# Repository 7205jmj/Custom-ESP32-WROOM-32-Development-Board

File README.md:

# Custom-ESP32-WROOM-32-Development-Board
A professionally designed ESP32-WROOM-32 Development Board created in KiCad for IoT, Embedded Systems, and Rapid Prototyping applications. This project aims to provide a compact, reliable, and cost-effective alternative to commercial ESP32 development boards while exposing essential GPIOs and integrating the required support circuitry for seamless programming and deployment.

Overview

Most ESP32 development boards available in the market include additional features that may not be required for every project. This custom board was designed to provide a clean and optimized ESP32 platform suitable for learning, prototyping, and product development.

The board integrates:

1.ESP32-WROOM-32 module
2.USB-powered operation
3.On-board 3.3V regulation
4.Auto-programming circuit
5.Reset and Boot buttons
6.Status indication LEDs
7.GPIO breakout headers
8.Compact 2-layer PCB layout

Hardware Specifications
Parameter	Specification
Module--->	ESP32-WROOM-32
CPU	---->Dual-Core Xtensa LX6
Clock Frequency------->	Up to 240 MHz
Flash Memory--------->	As per module variant
Operating Voltage	--->3.3V
Input Voltage---->	5V USB
Wireless-------->	Wi-Fi + Bluetooth
PCB Layers---------->	2
Design Software	--------->KiCad

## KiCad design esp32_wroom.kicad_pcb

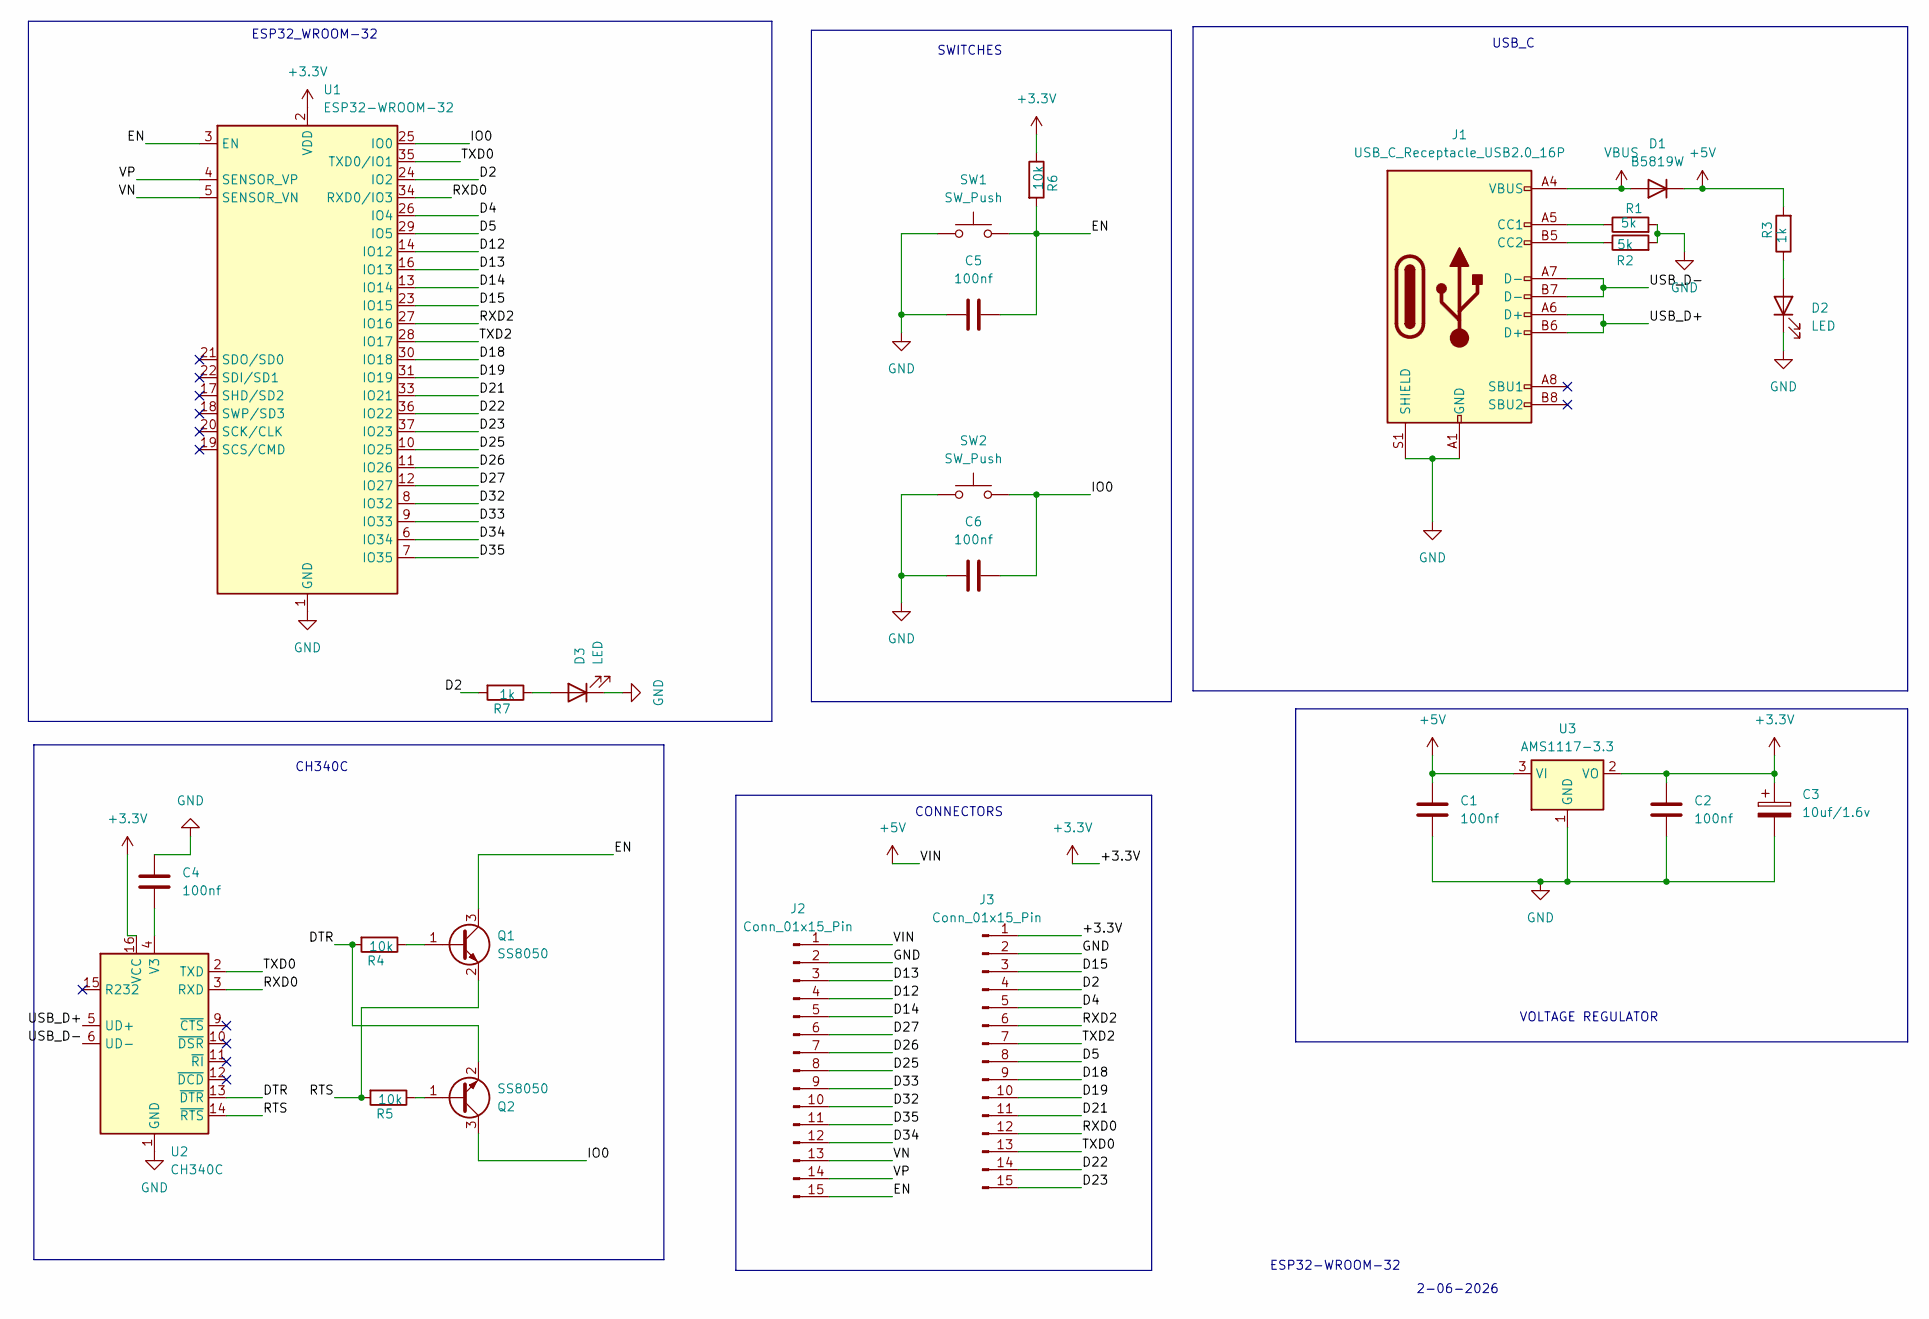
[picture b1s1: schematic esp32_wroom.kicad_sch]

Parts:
C1, C2, C4, C5, C6: 100nf; C_0603_1608Metric
C3: 10uf/1.6v; CP_EIA-3216-10_Kemet-I
D1: B5819W; D_SOD-123
D2, D3: LED; LED_0603_1608Metric
J1: USB_C_Receptacle_USB2.0_16P; USB_C_Receptacle_HRO_TYPE-C-31-M-12
J2, J3: Conn_01x15_Pin; PinHeader_1x15_P2.54mm_Vertical
Q1, Q2: SS8050; SOT-23
R1, R2: 5k; R_0603_1608Metric
R3, R7: 1k; R_0603_1608Metric
R4, R5, R6: 10k; R_0603_1608Metric
SW1, SW2: SW_Push; SW_Push_SPST_NO_Alps_SKRK
U1: ESP32-WROOM-32
U2: CH340C; SOIC-16_3.9x9.9mm_P1.27mm
U3: AMS1117-3.3; SOT-223-3_TabPin2

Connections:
+3.3V: C2.1, C3.1, J3.1, R6.1, U1.2 (VDD), U2.16 (VCC), U3.2 (VO)
+5V: C1.1, D1.1 (K), J2.1, R3.2, U3.3 (VI)
/D2: J3.4, R7.2, U1.24 (IO2)
/D4: J3.5, U1.26 (IO4)
/D5: J3.8, U1.29 (IO5)
/D12: J2.4, U1.14 (IO12)
/D13: J2.3, U1.16 (IO13)
/D14: J2.5, U1.13 (IO14)
/D15: J3.3, U1.23 (IO15)
/D18: J3.9, U1.30 (IO18)
/D19: J3.10, U1.31 (IO19)
/D21: J3.11, U1.33 (IO21)
/D22: J3.14, U1.36 (IO22)
/D23: J3.15, U1.37 (IO23)
/D25: J2.8, U1.10 (IO25)
/D26: J2.7, U1.11 (IO26)
/D27: J2.6, U1.12 (IO27)
/D32: J2.10, U1.8 (IO32)
/D33: J2.9, U1.9 (IO33)
/D34: J2.12, U1.6 (IO34)
/D35: J2.11, U1.7 (IO35)
/DTR: Q2.2 (E), R4.2, U2.13 (~DTR)
/EN: C5.2, J2.15, Q1.3 (C), R6.2, SW1.2, U1.3 (EN)
/IO0: C6.2, Q2.3 (C), SW2.2, U1.25 (IO0)
/RTS: Q1.2 (E), R5.2, U2.14 (~RTS)
/RXD0: J3.12, U1.34 (RXD0/IO3), U2.3 (RXD)
/RXD2: J3.6, U1.27 (IO16)
/TXD0: J3.13, U1.35 (TXD0/IO1), U2.2 (TXD)
/TXD2: J3.7, U1.28 (IO17)
/USB_D+: J1.A6 (D+), J1.B6 (D+), U2.5 (UD+)
/USB_D-: J1.A7 (D-), J1.B7 (D-), U2.6 (UD-)
/VN: J2.13, U1.5 (SENSOR_VN)
/VP: J2.14, U1.4 (SENSOR_VP)
GND: C1.2, C2.2, C3.2, C4.1, C5.1, C6.1, D2.1 (K), D3.1 (K), J1.A1 (GND), J1.A12 (GND), J1.B1 (GND), J1.B12 (GND), J1.S1 (SHIELD), J2.2, J3.2, R1.2, R2.2, SW1.1, SW2.1, U1.1 (GND), U1.15 (GND), U1.38 (GND), U1.39 (GND), U2.1 (GND), U3.1 (GND)
unnamed: D2.2 (A), R3.1
unnamed: D3.2 (A), R7.1
unnamed: J1.A5 (CC1), R1.1
unnamed: J1.B5 (CC2), R2.1
unnamed: Q1.1 (B), R4.1
unnamed: Q2.1 (B), R5.1
unnamed: C4.2, U2.4 (V3)
VBUS: D1.2 (A), J1.A4 (VBUS), J1.A9 (VBUS), J1.B4 (VBUS), J1.B9 (VBUS)

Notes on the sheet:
SWITCHES
ESP32_WROOM-32
ESP32-WROOM-32
CONNECTORS
CH340C
USB_C
2-06-2026
VOLTAGE REGULATOR

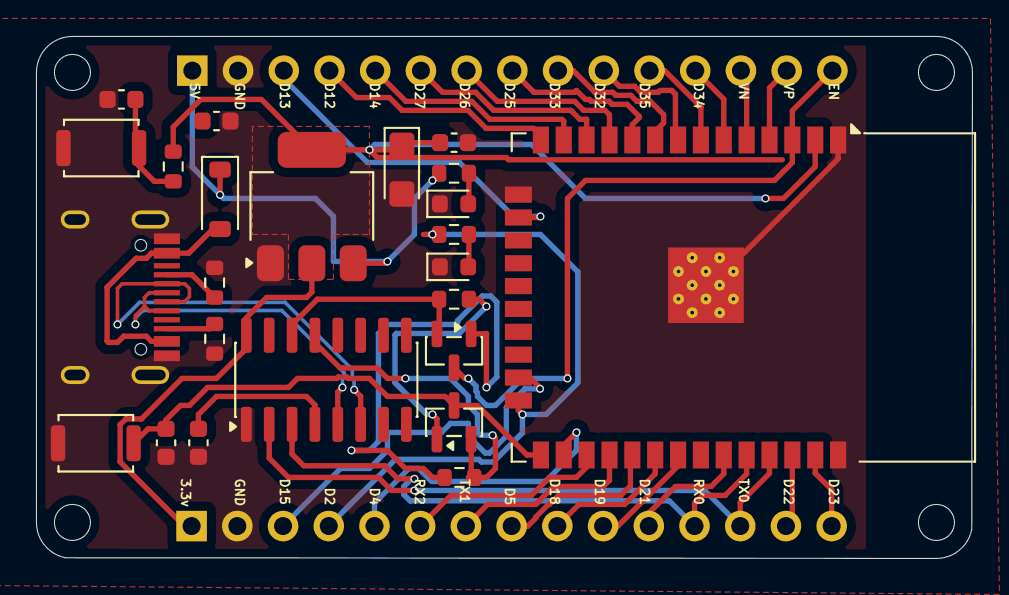
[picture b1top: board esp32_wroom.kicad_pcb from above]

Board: 2 copper layers, 52.0 x 29.0 mm, 26 parts (0 on the bottom side), 42 nets.

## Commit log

2026-06-02 Enhance README with project details and specs
    Added detailed project description, overview, and hardware specifications for the Custom ESP32-WROOM-32 Development Board.
